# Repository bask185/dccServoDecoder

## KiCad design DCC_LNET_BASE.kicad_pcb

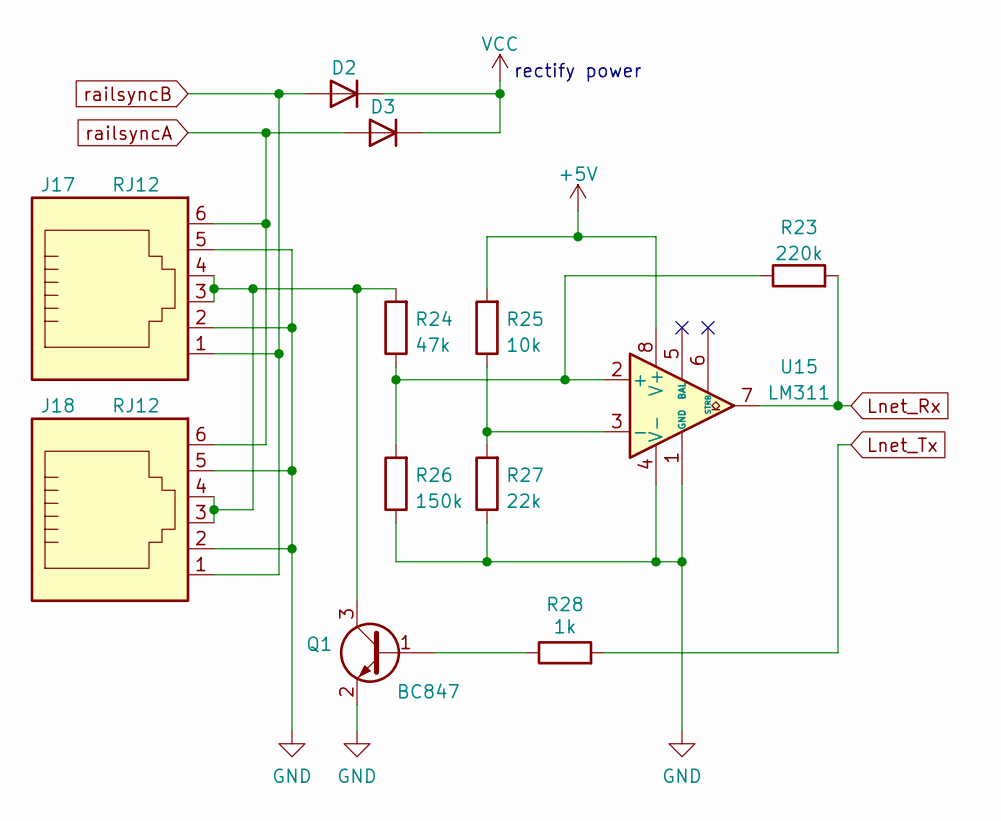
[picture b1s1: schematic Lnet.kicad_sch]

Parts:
D2, D3: D; D_SOD-323; JLCPCB Part# C2128
J17, J18: RJ12; RJ12_Amphenol_54601; JLCPCB Part# C77859
Q1: BC847; SOT-23; JLCPCB Part# C181140
R23: 220k; R_0805_2012Metric_Pad1.20x1.40mm_HandSolder; JLCPCB Part# C17556
R24: 47k; R_0805_2012Metric_Pad1.20x1.40mm_HandSolder; JLCPCB Part# C17713
R25: 10k; R_0805_2012Metric_Pad1.20x1.40mm_HandSolder; JLCPCB Part# C17414
R26: 150k; R_0805_2012Metric_Pad1.20x1.40mm_HandSolder; JLCPCB Part# C17470
R27: 22k; R_0805_2012Metric_Pad1.20x1.40mm_HandSolder; JLCPCB Part# C17560
R28: 1k; R_0603_1608Metric_Pad0.98x0.95mm_HandSolder; JLCPCB Part# C21190
U15: LM311; SOIC-8_3.9x4.9mm_P1.27mm; JLCPCB Part# C434495

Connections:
+5V: R25.2, U15.8 (V+); also elsewhere on the board
GND: J17.2, J17.5, J18.2, J18.5, Q1.2 (E), R26.1, R27.1, U15.1 (GND), U15.4 (V-); also elsewhere on the board
Lnet_Rx: R23.2, U15.7; also elsewhere on the board
Lnet_Tx: R28.2; also elsewhere on the board
unnamed: J17.3, J17.4, J18.3, J18.4, Q1.3 (C), R24.2
unnamed: Q1.1 (B), R28.1
unnamed: R23.1, R24.1, R26.2, U15.2 (+)
unnamed: R25.1, R27.2, U15.3 (-)
VCC: D2.1 (K), D3.1 (K); also elsewhere on the board
railsyncA: D3.2 (A), J17.6, J18.6
railsyncB: D2.2 (A), J17.1, J18.1

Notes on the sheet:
rectify power

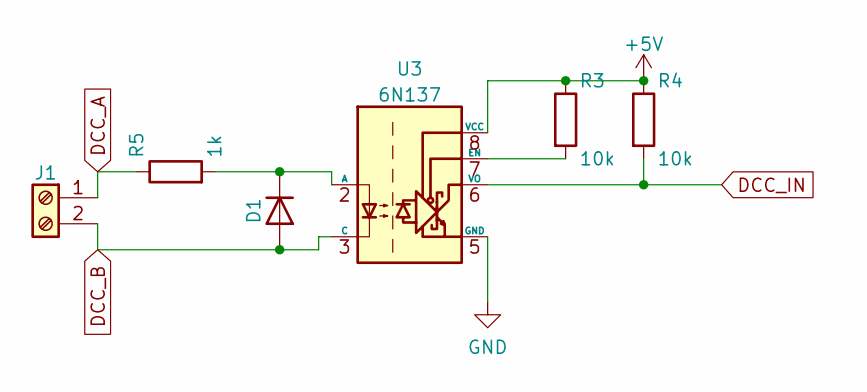
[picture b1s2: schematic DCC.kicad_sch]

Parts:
D1: D; D_SOD-323; JLCPCB Part# C2128
J1: Screw_Terminal_01x02; TerminalBlock_Phoenix_MKDS-1,5-2-5.08_1x02_P5.08mm_Horizont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
R3, R4: 10k; R_0805_2012Metric_Pad1.20x1.40mm_HandSolder; JLCPCB Part# C17414
R5: 1k; R_0805_2012Metric_Pad1.20x1.40mm_HandSolder; JLCPCB Part# C17513
U3: 6N137; SOP-8_6.62x9.15mm_P2.54mm; JLCPCB Part# C110020

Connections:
+5V: R3.1, R4.1, U3.8 (VCC); also elsewhere on the board
DCC_A: J1.1, R5.1; also elsewhere on the board
DCC_B: D1.2 (A), J1.2, U3.3 (C); also elsewhere on the board
DCC_IN: R4.2, U3.6 (VO); also elsewhere on the board
GND: U3.5 (GND); also elsewhere on the board
unnamed: D1.1 (K), R5.2, U3.2 (A)
unnamed: R3.2, U3.7 (EN)

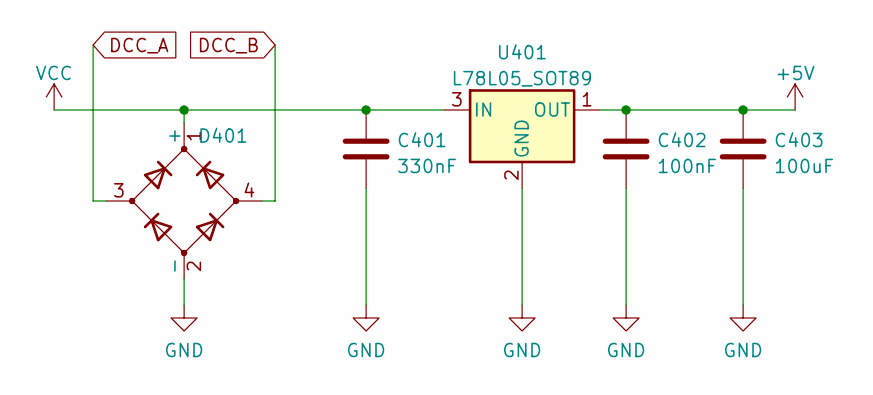
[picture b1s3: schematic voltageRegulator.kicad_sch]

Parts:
C401: 330nF; C_0603_1608Metric_Pad1.08x0.95mm_HandSolder; JLCPCB Part# C1615
C402: 100nF; C_0603_1608Metric_Pad1.08x0.95mm_HandSolder; JLCPCB Part# C14663
C403: 100uF; C_1206_3216Metric_Pad1.33x1.80mm_HandSolder; JLCPCB Part# C15008
D401: D_Bridge_+-AA; Diode_Bridge_Diotec_ABS; JLCPCB Part# C2488
U401: L78L05_SOT89; SOT-89-3; JLCPCB Part# C71136

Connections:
+5V: C402.1, C403.1, U401.1 (OUT); also elsewhere on the board
DCC_A: D401.3; also elsewhere on the board
DCC_B: D401.4; also elsewhere on the board
GND: C401.2, C402.2, C403.2, D401.2 (-), U401.2 (GND); also elsewhere on the board
VCC: C401.1, D401.1 (+), U401.3 (IN); also elsewhere on the board

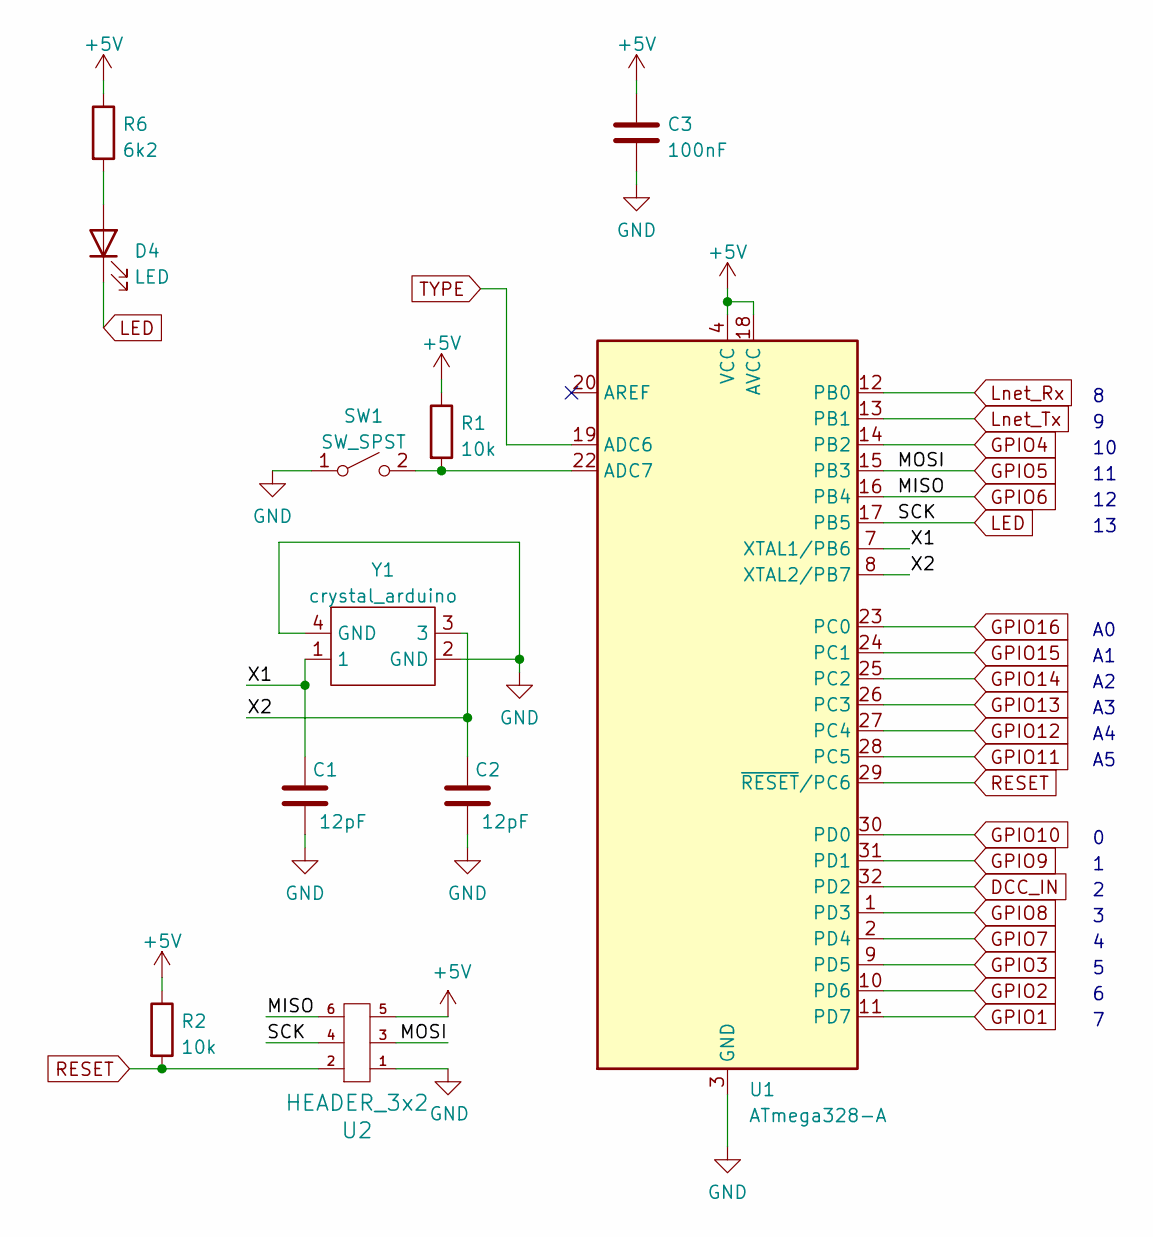
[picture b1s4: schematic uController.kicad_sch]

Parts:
C1, C2: 12pF; C_0402_1005Metric_Pad0.74x0.62mm_HandSolder; JLCPCB Part# C1547
C3: 100nF; C_0603_1608Metric_Pad1.08x0.95mm_HandSolder; JLCPCB Part# C14663
D4: LED; LED_0805_2012Metric_Pad1.15x1.40mm_HandSolder; JLCPCB Part# C84256
R1, R2: 10k; R_0402_1005Metric_Pad0.72x0.64mm_HandSolder; JLCPCB Part# C25744
R6: 6k2; R_0603_1608Metric_Pad0.98x0.95mm_HandSolder; JLCPCB Part# C4260
SW1: SW_SPST; SW_SPST_SKQG_WithStem; JLCPCB Part# C318884
U1: ATmega328-A; TQFP-32_7x7mm_P0.8mm; JLCPCB Part# C14877
U2: HEADER_3x2; PinSocket_2x03_P1.27mm_Vertical
Y1: crystal_arduino; JLCPCB Part# C13738

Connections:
+5V: C3.2, R1.1, R2.1, R6.1, U1.4 (VCC), U1.6 (VCC), U1.18 (AVCC), U2.5; also elsewhere on the board
/uController/X1: C1.2, U1.7 (XTAL1/PB6), Y1.1
/uController/X2: C2.2, U1.8 (XTAL2/PB7), Y1.3
DCC_IN: U1.32 (PD2); also elsewhere on the board
GND: C1.1, C2.1, C3.1, SW1.1 (A), U1.3 (GND), U1.5 (GND), U1.21 (GND), U2.1, Y1.2 (GND), Y1.4 (GND); also elsewhere on the board
GPIO1: U1.11 (PD7)
GPIO2: U1.10 (PD6)
GPIO3: U1.9 (PD5)
GPIO4: U1.14 (PB2)
GPIO5: U1.15 (PB3), U2.3
GPIO6: U1.16 (PB4), U2.6
GPIO7: U1.2 (PD4)
GPIO8: U1.1 (PD3)
GPIO9: U1.31 (PD1)
GPIO10: U1.30 (PD0)
GPIO11: U1.28 (PC5)
GPIO12: U1.27 (PC4)
GPIO13: U1.26 (PC3)
GPIO14: U1.25 (PC2)
GPIO15: U1.24 (PC1)
GPIO16: U1.23 (PC0)
LED: D4.1 (K), U1.17 (PB5), U2.4
Lnet_Rx: U1.12 (PB0); also elsewhere on the board
Lnet_Tx: U1.13 (PB1); also elsewhere on the board
unnamed: D4.2 (A), R6.2
unnamed: R1.2, SW1.2 (B), U1.22 (ADC7)
RESET: R2.2, U1.29 (~RESET/PC6), U2.2
TYPE: U1.19 (ADC6)

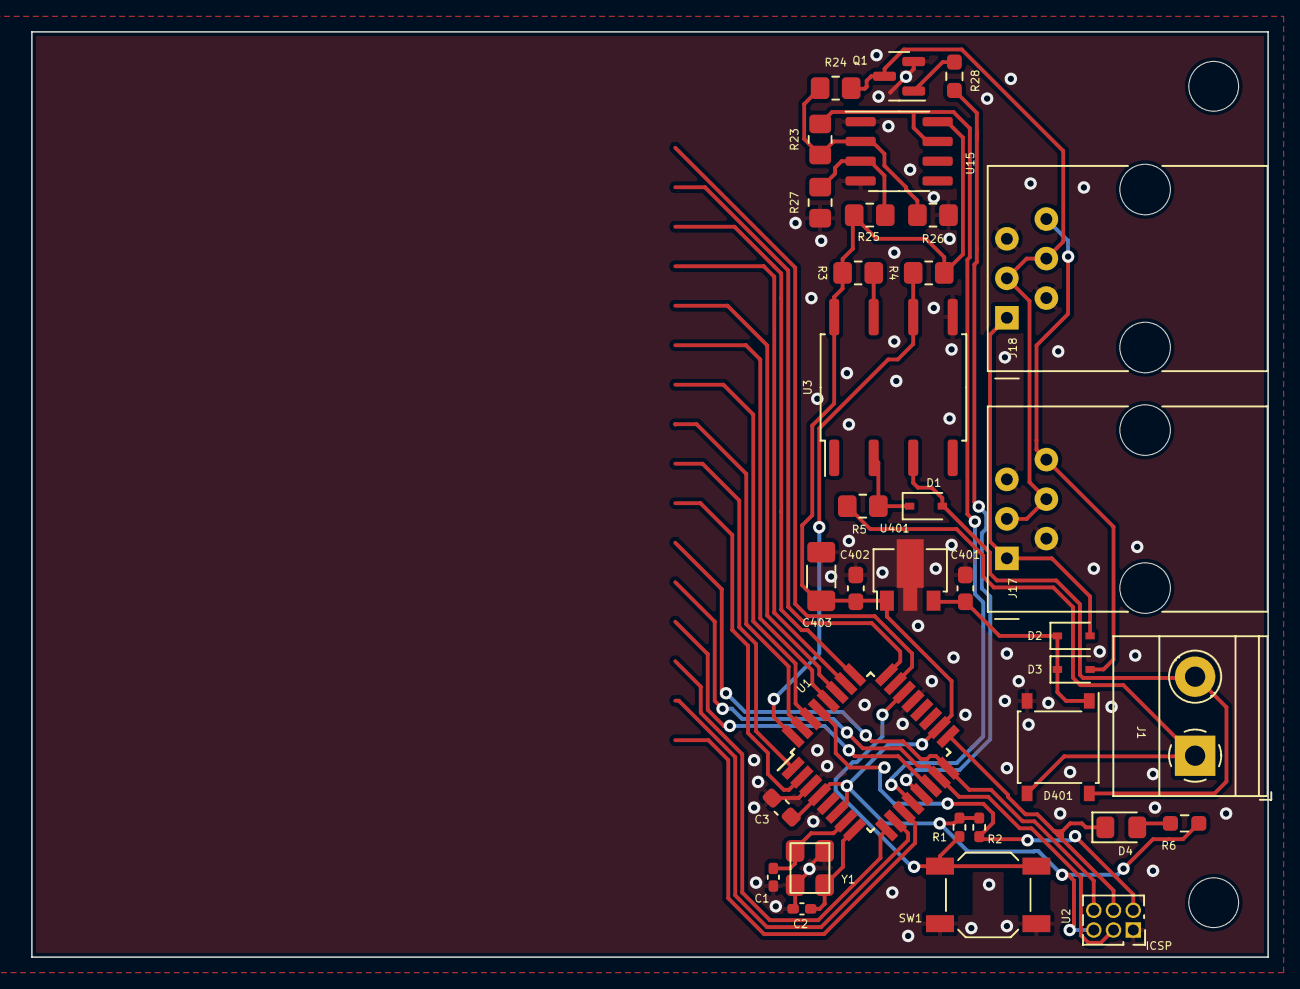
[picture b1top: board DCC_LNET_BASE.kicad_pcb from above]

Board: 2 copper layers, 79.5 x 59.5 mm, 34 parts (0 on the bottom side), 24 nets.

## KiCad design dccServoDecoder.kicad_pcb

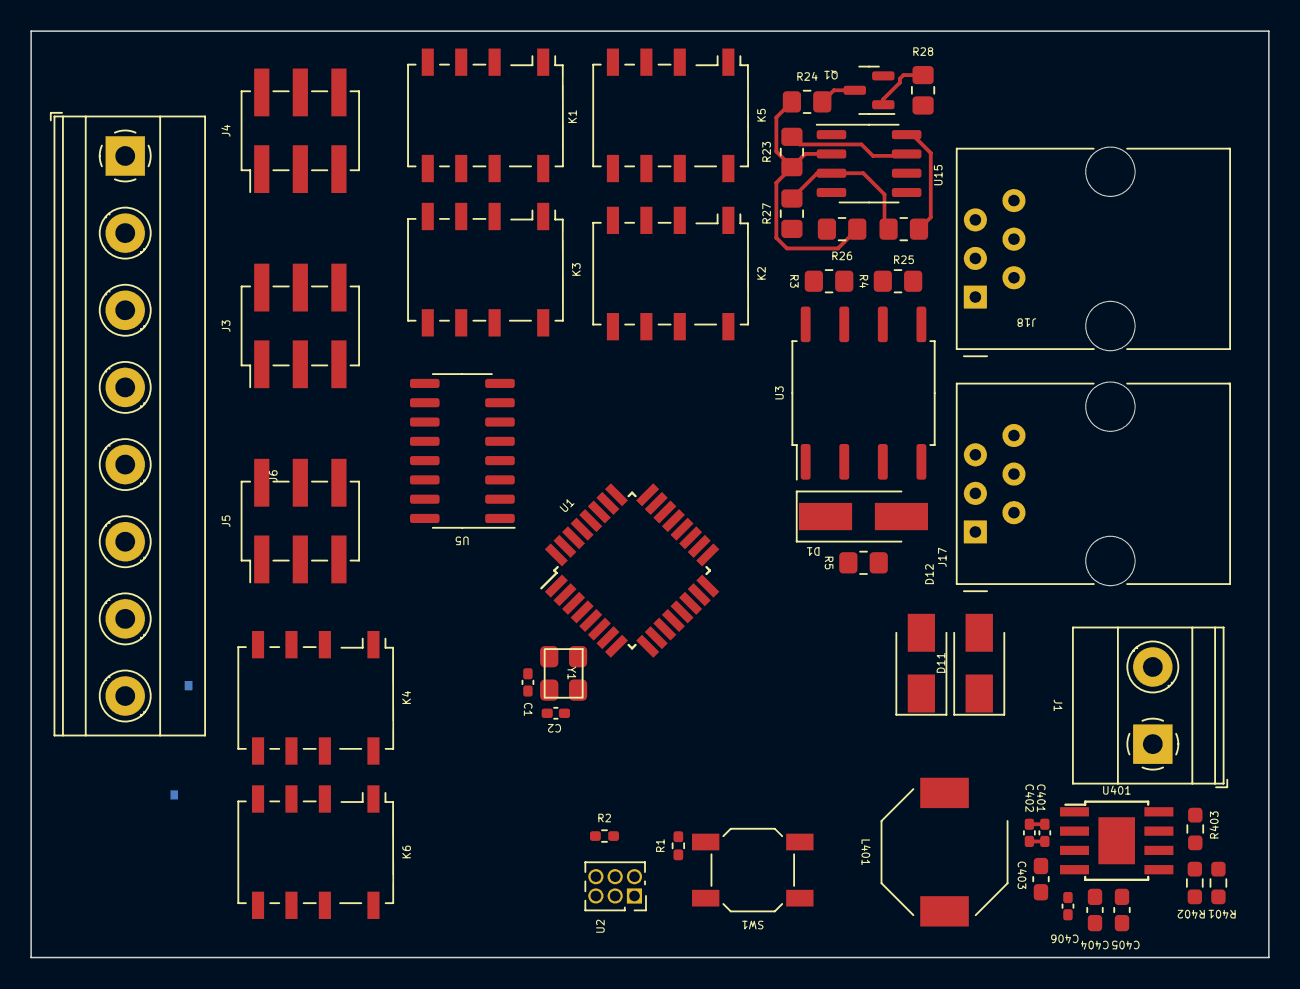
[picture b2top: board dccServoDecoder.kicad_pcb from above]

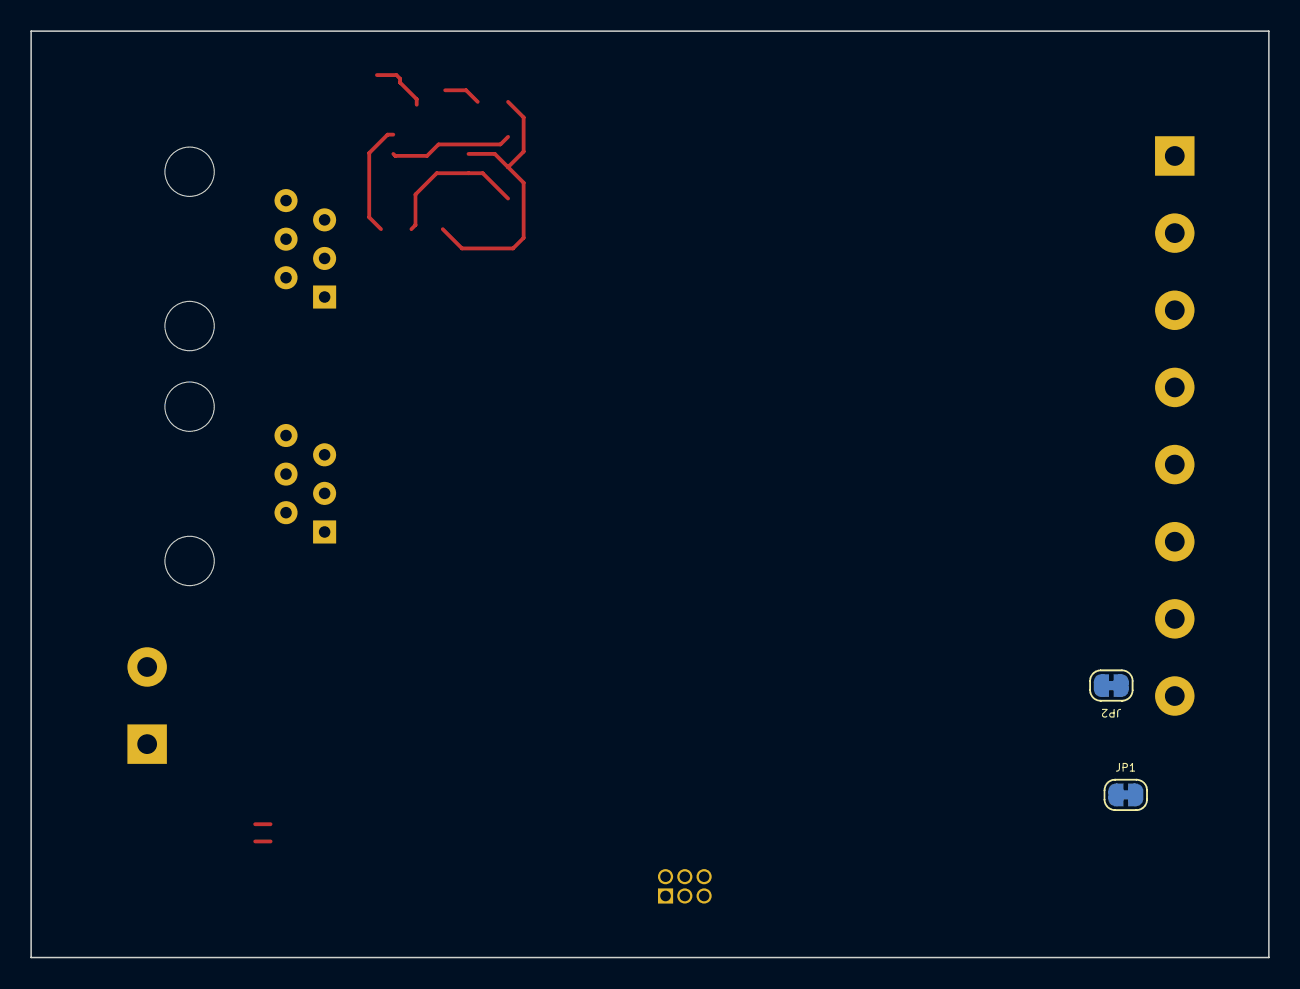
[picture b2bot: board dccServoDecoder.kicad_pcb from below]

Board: 2 copper layers, 81.5 x 61.0 mm, 50 parts (2 on the bottom side), 49 nets.

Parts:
C1, C2: 12pF; C_0402_1005Metric_Pad0.74x0.62mm_HandSolder
C401, C406: 100nF; C_0402_1005Metric_Pad0.74x0.62mm_HandSolder
C402: 22nF; C_0402_1005Metric_Pad0.74x0.62mm_HandSolder
C403, C404, C405: 22uF; C_0603_1608Metric_Pad1.08x0.95mm_HandSolder
D1: D; D_SMA_Handsoldering
D11, D12: D; D_SMA
J1: Screw_Terminal_01x02; TerminalBlock_Phoenix_MKDS-1,5-2-5.08_1x02_P5.08mm_Horizont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
J3, J4, J5: Conn_02x03_Odd_Even; PinHeader_2x03_P2.54mm_Vertical_SMD
J6: Screw_Terminal_01x08; TerminalBlock_Phoenix_MKDS-1,5-8-5.08_1x08_P5.08mm_Horizont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
J17, J18: RJ12; RJ12_Amphenol_54601
JP1, JP2: SolderJumper_2_Bridged; SolderJumper-2_P1.3mm_Bridged_RoundedPad1.0x1.5mm
K1, K2, K3, K4, K5, K6: G6K-2; Relay_DPDT_Omron_G6K-2F-Y
L401: L; L_Bourns-SRU8028_8.0x8.0mm
Q1: BC847; SOT-23
R1, R2: 10k; R_0402_1005Metric_Pad0.72x0.64mm_HandSolder
R3, R4, R25: 10k; R_0805_2012Metric_Pad1.20x1.40mm_HandSolder
R5, R28: 1k; R_0805_2012Metric_Pad1.20x1.40mm_HandSolder
R23: 220k; R_0805_2012Metric_Pad1.20x1.40mm_HandSolder
R24: 47k; R_0805_2012Metric_Pad1.20x1.40mm_HandSolder
R26: 150k; R_0805_2012Metric_Pad1.20x1.40mm_HandSolder
R27: 22k; R_0805_2012Metric_Pad1.20x1.40mm_HandSolder
R401: 220k; R_0603_1608Metric_Pad0.98x0.95mm_HandSolder
R402: 150k; R_0603_1608Metric_Pad0.98x0.95mm_HandSolder
R403: 20k; R_0603_1608Metric_Pad0.98x0.95mm_HandSolder
SW1: SW_SPST; SW_SPST_SKQG_WithStem
U1: ATmega328-A; TQFP-32_7x7mm_P0.8mm
U2: HEADER_3x2; PinSocket_2x03_P1.27mm_Vertical
U3: 6N137; SOP-8_6.62x9.15mm_P2.54mm
U5: ULN2003A; SOIC-16_3.9x9.9mm_P1.27mm
U15: LM311; SOIC-8_3.9x4.9mm_P1.27mm
U401: MT2499A; TI_SO-PowerPAD-8
Y1: crystal_arduino

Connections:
+5V: C404.1, C405.1, C406.1, J3.3, J3.4, J4.3, J4.4, J5.3, J5.4, K1.1, K2.1, K3.1, K4.1, K5.1, K6.1, L401.2, R1.1, R2.1, R3.1, R4.1, R25.2, R401.1, R402.2, U1.4 (VCC), U1.6 (VCC), U1.18 (AVCC), U2.5, U3.8 (VCC), U5.9 (COM), U15.8 (V+)
+12V: D11.1 (K), D12.1 (K)
/uController/X1: C1.2, U1.7 (XTAL1/PB6), Y1.1
/uController/X2: C2.2, U1.8 (XTAL2/PB7), Y1.3
COM_A: J6.7, JP1.2 (B), K1.4, K2.4, K3.4, K4.4, K5.4, K6.4
COM_B: J6.8, JP2.2 (B), K1.2, K2.2, K3.2, K4.2, K5.2, K6.2
DCC_A: J1.2, JP1.1 (A), R5.1
DCC_B: D1.2 (A), J1.1, JP2.1 (A), U3.3 (C)
DCC_IN: R4.2, U1.32 (PD2), U3.6 (VO)
GND: C1.1, C2.1, C403.2, C404.2, C405.2, C406.2, J3.1, J3.2, J4.1, J4.2, J5.1, J5.2, J17.2, J17.5, J18.2, J18.5, Q1.2 (E), R26.1, R27.1, R403.2, SW1.1 (A), U1.3 (GND), U1.5 (GND), U1.21 (GND), U2.1, U3.5 (GND), U5.8 (GND), U15.1 (GND), U15.4 (V-), U401.4 (GND), U401.9 (GND), Y1.2 (GND), Y1.4 (GND)
Lnet_Rx: R23.2, U15.7
unnamed: C401.1, C402.1, U401.1 (BS)
unnamed: C401.2, C402.2, L401.1, U401.3 (SW)
unnamed: C403.1, U401.2 (Vin), U401.7 (EN)
unnamed: D1.1 (K), R5.2, U3.2 (A)
unnamed: J17.3, J17.4, J18.3, J18.4, Q1.3 (C), R24.2
unnamed: R1.2, SW1.2 (B), U1.22 (ADC7)
unnamed: R3.2, U3.7 (EN)
unnamed: R23.1, R24.1, R26.2, U15.2 (+)
unnamed: R25.1, R27.2, U15.3 (-)
unnamed: Q1.1 (B), R28.1
unnamed: R401.2, R402.1, R403.1, U401.5 (FB)
RESET: R2.2, U1.29 (~RESET/PC6), U2.2
coil1: K1.8, U5.11 (O6)
coil2: K3.8, U5.12 (O5)
coil3: K5.8, U5.13 (O4)
coil4: K2.8, U5.14 (O3)
coil5: K4.8, U5.15 (O2)
coil6: K6.8, U5.16 (O1)
frog1: J6.1, K1.3
frog2: J6.2, K3.3
frog3: J6.3, K5.3
frog4: J6.4, K2.3
frog5: J6.5, K4.3
frog6: J6.6, K6.3
railsyncA: D12.2 (A), J17.6, J18.6
railsyncB: D11.2 (A), J17.1, J18.1
relay1: U1.15 (PB3), U2.3, U5.6 (I6)
relay2: U1.16 (PB4), U2.6, U5.5 (I5)
relay3: U1.17 (PB5), U2.4, U5.4 (I4)
relay4: U1.23 (PC0), U5.3 (I3)
relay5: U1.24 (PC1), U5.2 (I2)
relay6: U1.25 (PC2), U5.1 (I1)
servo1: J3.6, U1.14 (PB2)
servo2: J3.5, U1.13 (PB1)
servo3: J4.6, U1.12 (PB0)
servo4: J4.5, U1.11 (PD7)
servo5: J5.6, U1.10 (PD6)
servo6: J5.5, U1.9 (PD5)

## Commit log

2023-04-05 finalized default template
